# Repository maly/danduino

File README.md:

# danduino
DAN64 in Arduino (from https://github.com/reidrac/dan64)

Original by Juan J. Martínez: https://www.usebox.net/jjm/dan64/

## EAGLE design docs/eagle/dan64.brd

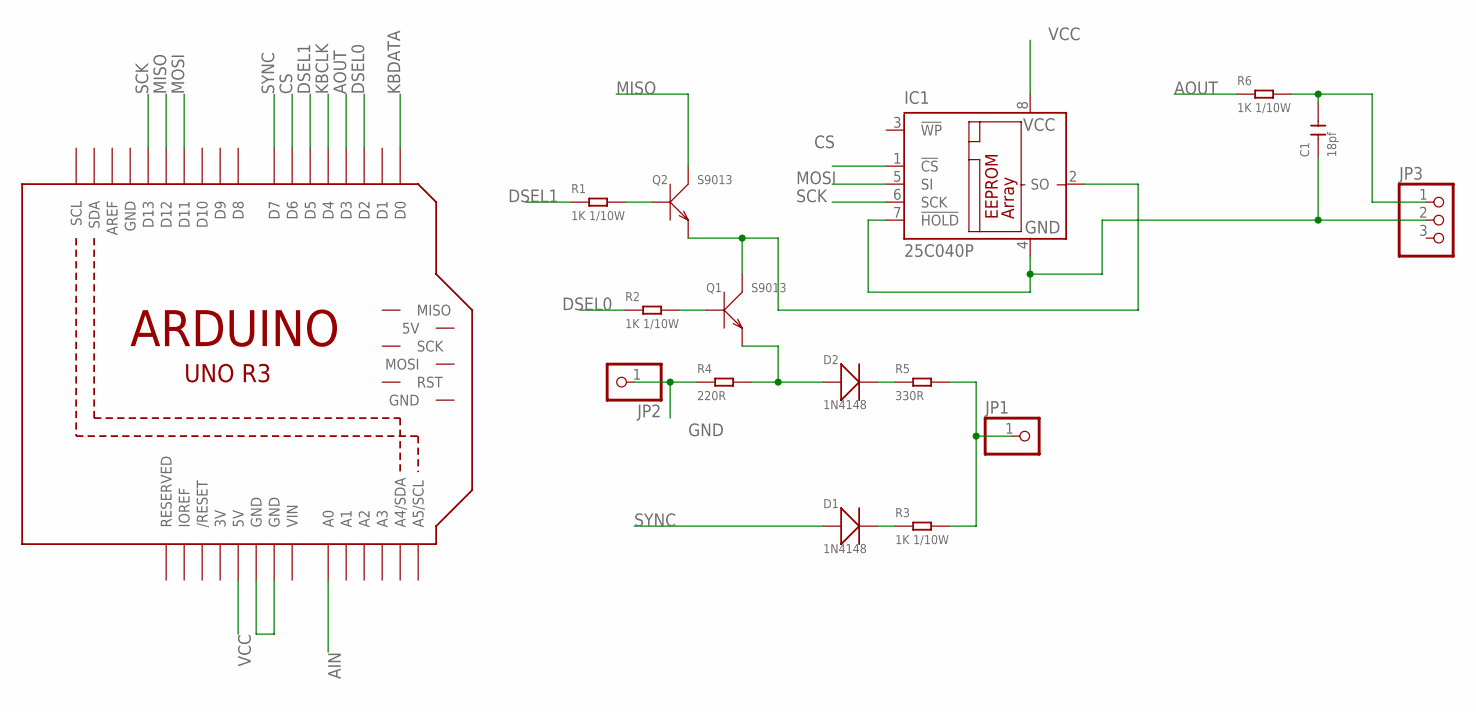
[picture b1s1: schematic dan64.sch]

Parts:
C1: 18pf; C0402
D1, D2: 1N4148; LL-34
IC1: 25C040P; DIL8
JP1, JP2: PINHD-1X1; 1X01
JP3: PINHD-1X3; 1X03
M1: ARDUINO_R3_ICSP; ARDUINOR3_ICSP
Q1, Q2: S9013; SOT-23
R1, R2, R3, R6: 1K 1/10W; R0603
R4: 220R; R0603
R5: 330R; R0603

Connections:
3V: M1.3V
AIN: M1.A0
AOUT: M1.D3, R6.1
CS: IC1.1 (!CS), M1.D6
DSEL0: M1.D2, R2.1
DSEL1: M1.D5, R1.1
GND: C1.1, IC1.4 (GND), IC1.7 (!HOLD), JP2.1, JP3.2, M1.GND, M1.GND@1 (GND), M1.GND@3 (GND), R4.1
KBCLK: M1.D4
KBDATA: M1.D0
MISO: M1.D12, Q2.3 (C)
MOSI: IC1.5 (SI), M1.D11
unnamed: D2.C (-), R5.1
unnamed: D1.C (-), R3.1
unnamed: JP1.1, R3.2, R5.2
unnamed: D2.A (+), Q1.2 (E), R4.2
unnamed: Q1.1 (B), R2.2
unnamed: C1.2, JP3.1, R6.2
unnamed: Q2.1 (B), R1.2
unnamed: IC1.2 (SO), Q1.3 (C), Q2.2 (E)
SCK: IC1.6 (SCK), M1.D13
SYNC: D1.A (+), M1.D7
VCC: IC1.8 (VCC), M1.5V
VIN: M1.VIN

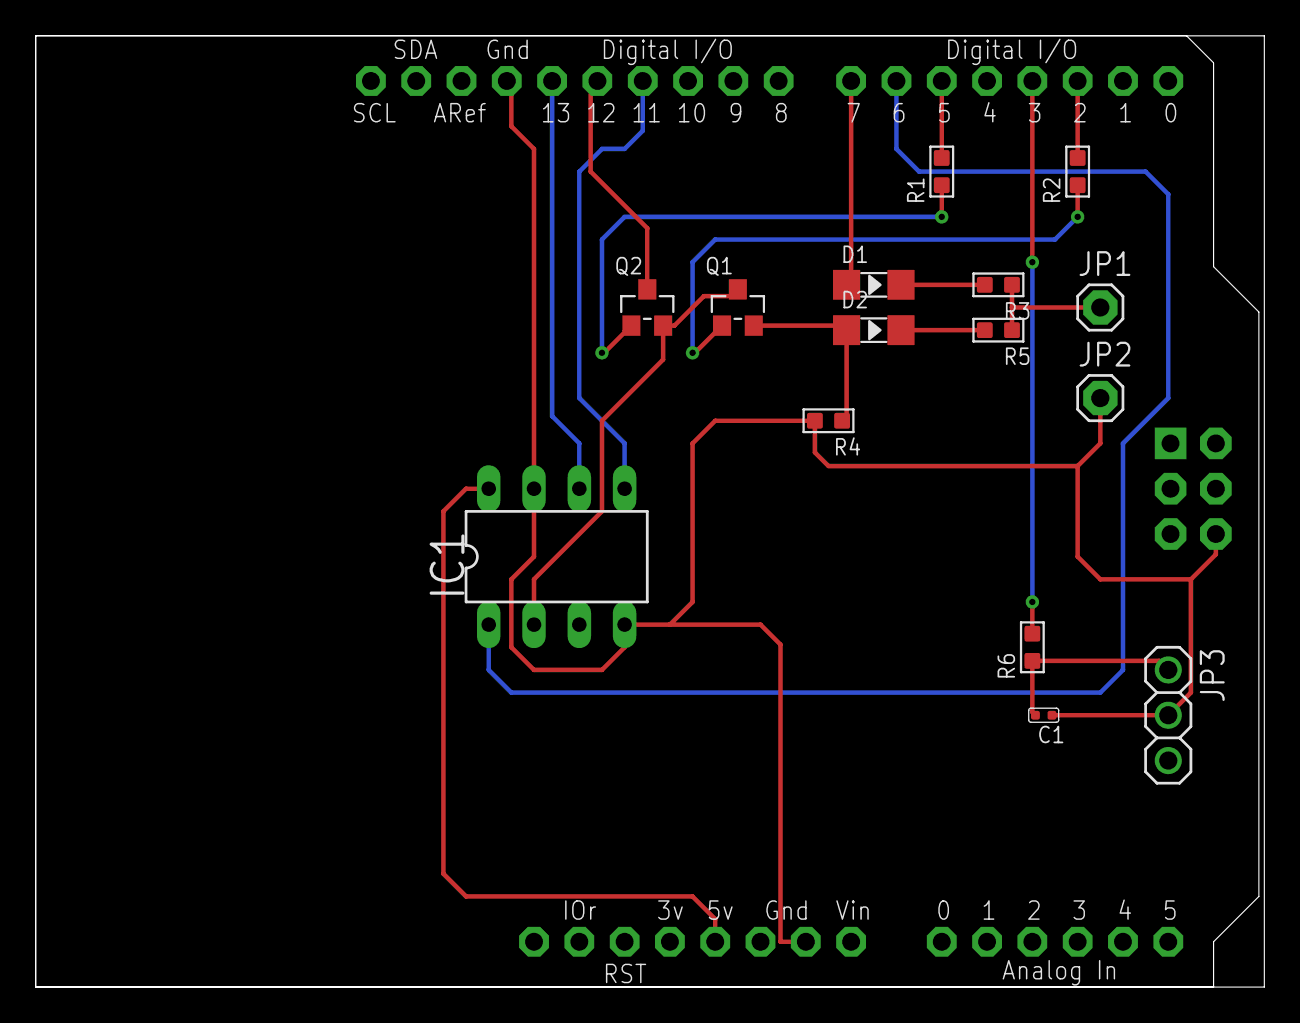
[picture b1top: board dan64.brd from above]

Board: 2 copper layers, 68.9 x 53.3 mm, 16 parts (0 on the bottom side), 18 nets.

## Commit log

2018-01-27 Initial
2018-01-27 Docs
2018-02-17 README
